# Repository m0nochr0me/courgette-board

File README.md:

Just another board for ATMEGA168/328 with RJ12 connector and four WS2812B LEDs

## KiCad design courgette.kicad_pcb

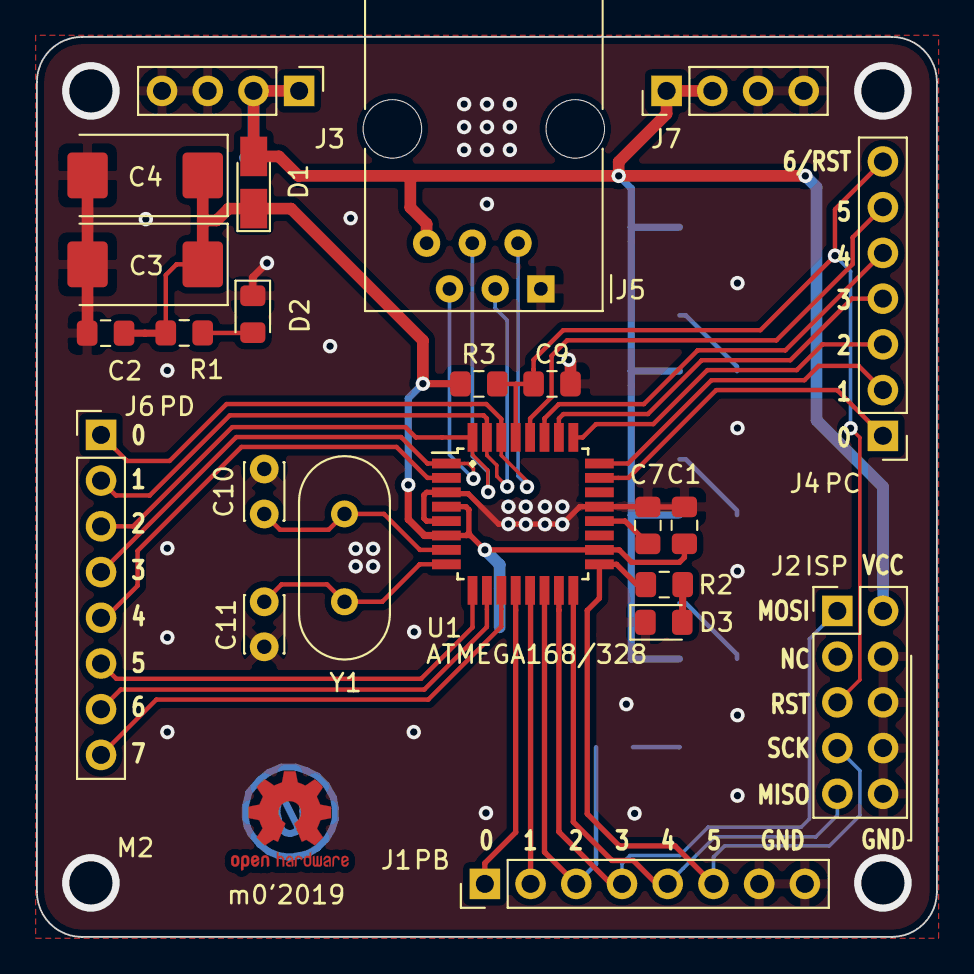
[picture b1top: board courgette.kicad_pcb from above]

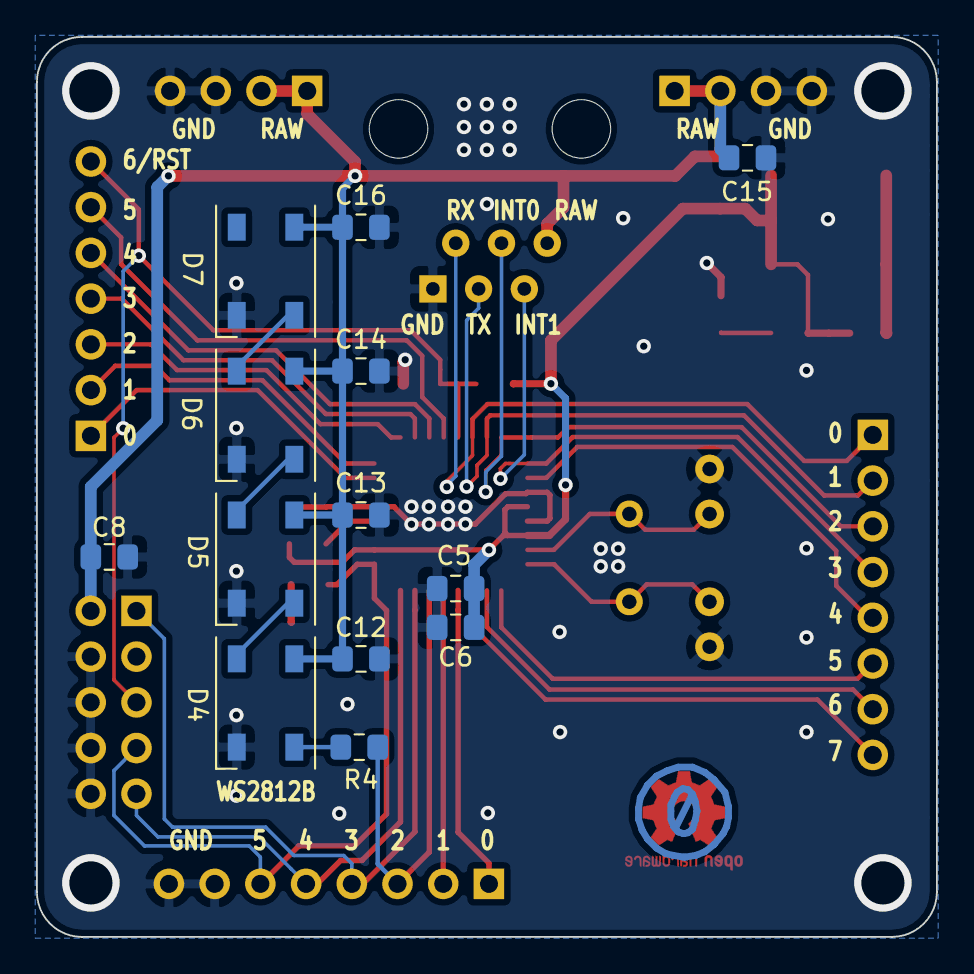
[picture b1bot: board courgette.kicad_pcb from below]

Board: 2 copper layers, 50.0 x 50.0 mm, 36 parts (13 on the bottom side), 33 nets.

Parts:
C1, C2, C7, C9: 0.1; C_0805_2012Metric_Pad1.15x1.40mm_HandSolder
C3, C4: 100; CP_EIA-7343-31_Kemet-D_Pad2.25x2.55mm_HandSolder
C5, C6, C8, C12, C13, C14, C15, C16: 1; C_0805_2012Metric_Pad1.15x1.40mm_HandSolder
C10, C11: 22pf; C_Disc_D3.0mm_W2.0mm_P2.50mm
D1: 1N4148; D_MicroMELF_Hadsoldering
D2, D3: LED_Small; LED_0805_2012Metric_Pad1.15x1.40mm_HandSolder
D4, D5, D6, D7: WS2812B; LED_WS2812B_PLCC4_5.0x5.0mm_P3.2mm
J1: PB; PinHeader_1x08_P2.54mm_Vertical
J2: ISP; PinHeader_2x05_P2.54mm_Vertical
J3, J7: PWR; PinHeader_1x04_P2.54mm_Vertical
J4: PC; PinHeader_1x07_P2.54mm_Vertical
J5: EXT; RJ12_Amphenol_54601
J6: PD; PinHeader_1x08_P2.54mm_Vertical
R1, R2, R4: 330; R_0805_2012Metric_Pad1.15x1.40mm_HandSolder
R3: 10k; R_0805_2012Metric_Pad1.15x1.40mm_HandSolder
U1: ATmega328-AU; TQFP-32_7x7mm_P0.8mm
Y1: 8MHz; Crystal_HC49-U_Vertical

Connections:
/INT0: J5.4, J6.3, U1.32
/INT1: J5.5, J6.4, U1.1
/MISO: J1.5, J2.9, U1.16
/MOSI: J1.4, J2.1, U1.15
/PB0: J1.1, U1.12
/PB1: J1.2, U1.13
/PC0: J4.1, U1.23
/PC1: J4.2, U1.24
/PC2: J4.3, U1.25
/PC3: J4.4, U1.26
/PC4: J4.5, U1.27
/PC5: J4.6, U1.28
/PD4: J6.5, U1.2
/PD5: J6.6, U1.9
/PD6: J6.7, U1.10
/PD7: J6.8, U1.11
/PIX: J1.3, R4.1, U1.14
/RAW: C8.1, C12.1, C13.1, C14.1, C15.1, C16.1, D1.2, D4.1, D5.1, D6.1, D7.1, J2.2, J3.1, J3.2, J5.6, J7.1, J7.2
/RST: C9.1, J2.5, J4.7, R3.2, U1.29
/RXD: J5.2, J6.1, U1.30
/SCK: J1.6, J2.7, R2.1, U1.17
/TXD: J5.3, J6.2, U1.31
/XTAL1: C10.1, U1.7, Y1.1
/XTAL2: C11.1, U1.8, Y1.2
GND: C1.2, C2.2, C3.2, C4.2, C5.2, C6.2, C7.2, C8.2, C9.2, C10.2, C11.2, C12.2, C13.2, C14.2, C15.2, C16.2, D2.1, D3.1, D4.3, D5.3, D6.3, D7.3, J1.7, J1.8, J2.4, J2.6, J2.8, J2.10, J3.3, J3.4, J5.1, J7.3, J7.4, U1.3, U1.5, U1.21
unnamed: C7.1, U1.20
unnamed: D2.2, R1.2
unnamed: D3.2, R2.2
unnamed: D4.2, D5.4
unnamed: D4.4, R4.2
unnamed: D5.2, D6.4
unnamed: D6.2, D7.4
VCC: C1.1, C2.1, C3.1, C4.1, C5.1, C6.1, D1.1, R1.1, R3.1, U1.4, U1.6, U1.18

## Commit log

2019-09-16 Add schematics image
2019-09-16 Added licensing information
2019-09-16 Added renders

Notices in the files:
README.md:
https://licensebuttons.net/p/zero/1.0/80x15.png
